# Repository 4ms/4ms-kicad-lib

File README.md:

4ms-kicad-lib
-------------

Intro:
-----

4ms-kicad-lib is a collection of symbol and footprint libraries for KiCad 10.
These libraries were created by and for people working at [4ms
Company](https://4mscompany.com). We share them publicly in hopes they help
others design great circuits. Have fun.

There are also some legacy symbol libraries for KiCad 5.1.x in
`symbols-legacy`, but they will not be updated or maintained, and they aren't
included in the KiCad Plugin and Content Manager archive.

We tried to follow the KiCad Library Conventions, although we made breaks from
that where it made sense. We also tried to keep the look and feel of the
official KiCad symbols, to make using this library and the official KiCad
libraries seamless.

What's in here:
--------------

__Libraries (KiCad PCM archive):__

`symbols`: The symbol library (schematic symbols). As of May 2020, we have
switched to using a unique symbol for each physical component that might appear
on a BOM line.

`footprints`: The footprint library (pcb). Library names tend to follow the
standard of the official KiCad .pretty libraries, but with a "4ms_" prefix. One
interesting library is the `4ms_Faceplate.pretty`: these are intended to be
used with our faceplate generation scripts. Each component is a hole or slot
that's the correct size for a particular faceplate-mounted component. 

`3dmodels`: 3D models for the footprints, organized similar to how the official
KiCad 3dmodels are organized.

__Other stuff (not in KiCad PCM archive):__

`design-blocks`: These are design blocks that we re-use. We're still new to
this workflow, so it's not part of the PCM release until we figure out how to
best package these.

`symbols-legacy/kicad5-2021`: The legacy symbol library for KiCad 5.1.x. This
is a snapshot of the libraries at Nov 19, 2021. It will not be updated or
maintained.

`symbols-legacy/kicad5-2019`: An even older library using non-atomic symbols
(generic resistor, capacitor, etc). This was deprecated in May 2020. It is no
longer maintained or updated.

`footprints-legacy`: The legacy footprint library, not really of much use since
PCBs embed the footprints they used.

`packages3d`: Legacy random 3d models, please verify dimensions before relying
on the accuracy of these models.

`lib-table-files`: The library table files. People working on 4ms projects
should copy these into a project directory (see Option B, Step 3 below).

`schematic-blocks`: KiCad schematic sheets of basic circuits we use over and
over. These building blocks are intended to be used as hierarchical sheets, or
just copy/pasted into your design. They are in KiCad 5 format at the moment but
can be used by KiCad 6 as well.

How to Install Symbol and Footprint Libraries:
----------

There are two ways to install these libraries:

  * **Option A: KiCad's Plugin and Content Manager (PCM).** Easiest. Recommended
    unless you work at 4ms, or are very comfortable with KiCad library management.
  * **Option B: Clone this git repo.** Gets you the latest changes as soon as
    they're pushed, but you have to manually manage this library in KiCad. This
    is what people working at 4ms use.

### Option A: Install with the Plugin and Content Manager

__Step 1) Install the package__

  * In the KiCad project window, open the `Plugin and Content Manager`.
  * Select the `Libraries` tab and find `4ms Kicad Libraries`.
  * Click `Install`, then click `Apply Pending Changes`.
  * Restart KiCad.

KiCad will add all the symbol and footprint libraries to your global
library tables, and the 3D models are installed and linked automatically.

__Step 2) Find the libraries__

PCM adds each library with a `PCM_` prefix on its nickname, so
`4ms_Resistor` shows up as `PCM_4ms_Resistor` in the symbol chooser and
footprint browser. The symbols in the PCM package already link to the
`PCM_4ms_...` footprint libraries, so footprints are filled in for you when you
place a symbol.

__Notes__

  * The footprint links in the symbols assume KiCad's default PCM settings:
    "Automatically add installed libraries to global library table" turned on,
    and "Library nickname prefix" set to `PCM_`. Both are in KiCad's
    Preferences, under `Plugin and Content Manager`. If you've changed either
    of these, you'll need to add the libraries to your tables yourself, using
    the `PCM_` prefix on each nickname.
  * PCM installs files into your `${KICAD10_3RD_PARTY}` folder (on macOS:
    `~/Documents/KiCad/10.0/3rdparty`), in subfolders named
    `com_github_4ms_4ms-kicad-lib`.
  * You can also download the `.zip` from this repo's
    [Releases page](https://github.com/4ms/4ms-kicad-lib/releases) and install
    it with `Install from File...` in the Plugin and Content Manager.
  * Updates show up in the Plugin and Content Manager when we publish a new
    release.

### Option B: Clone the git repo

__Step 1) Download the libraries__

Clone this repo (or download it as a zip) and save it wherever you keep your
KiCad libraries.

__Step 2) Set the `KICAD_4MS_LIBS` path variable__

The footprints find their 3D models through this variable, and the library
table files use it too, so set it even if you add the libraries by hand. You
only need to do this once, it's a global setting.

  * In the KiCad project window, select `Configure Paths...` in the
    `Preferences` menu.
  * Add a new entry named `KICAD_4MS_LIBS`, and set its path to the
    4ms-kicad-lib folder, for example
    `/Users/YOURUSERNAME/MyKiCadProjects/4ms-kicad-lib`

__Step 3) Add the libraries to your library tables__

To add **all** the 4ms libraries to a project (what anyone working at 4ms will
want), copy the two files in `lib-table-files/` (`fp-lib-table` and
`sym-lib-table`) into your project folder. Or you can add those library table files
to an existing project:

Or, to add only some libraries, or to add them globally:

  * Select `Manage Symbol Libraries` (in the schematic editor) or `Manage
    Footprint Libraries` (in the PCB editor) in the Preferences menu.
  * Select the Global tab to use these libraries in all your projects, or
    the Project tab to use them only in the current project.
  * Click the folder icon below the list, and browse to the libraries you want
    to add. On macOS you can Cmd-click to select several at once.
  * Repeat for both the symbol libraries and the footprint libraries.
  * Keep the nicknames as they are (e.g. `4ms_Resistor`), because the symbols
    link to footprints by those names.

### A note on mixing the two

The PCM package and the git repo use different library nicknames
(`PCM_4ms_Resistor` vs. `4ms_Resistor`), and each version's symbols link to
its own footprints. You can have both installed, but stick to one per project,
or a symbol from one may point to a footprint library that the project doesn't
use.

More resources
----------

The symbol library works well with our BOM scripts (exporting files compatible
with JLCPCB, for example). We also have a series of scripts that generate a
Eurorack faceplate from a PCB, and more. These can be found in our script repo:
https://github.com/4ms/4ms-kicad-script

LICENSE
-------

These are in the public domain under the Unlicense.

TODO
----

  * Add better descriptions for each library

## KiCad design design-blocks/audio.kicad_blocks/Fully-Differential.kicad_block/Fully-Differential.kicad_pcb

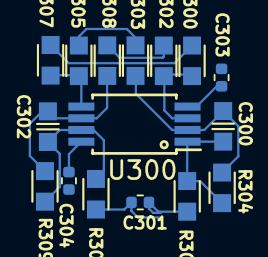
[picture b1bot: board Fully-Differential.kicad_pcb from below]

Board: 2 copper layers, 16 parts (16 on the bottom side), 14 nets.

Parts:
C300, C302: 100pF_0603_50V; C_0603
C301: 10nF_0402_16V; C_0402
C303, C304: 100nF_0402_16V; C_0402
R300, R303, R305, R308: 100k_0603_0.1%; R_0603
R301, R306: 47Ω_0603; R_0603
R302, R304, R307, R309: 14k_0603_0.1%; R_0603
U300: TL072H; TSSOP-8_4.4x3mm_Pitch0.65mm

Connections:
+12V_B: C304.1, U300.8 (V+)
-12VA_B: C303.1, U300.4 (V-)
/Audio/In1_A+: R300.1, R308.1
/Audio/In1_A-: R303.1, R305.1
/Audio/VCOMAD: R302.2, R307.2
/Audio/VIN4+: C301.1, R301.2
/Audio/VIN4-: C301.2, R306.2
GNDA: C303.2, C304.2
unnamed: C300.2, R301.1, R304.2, U300.1
unnamed: C302.2, R306.1, R309.2, U300.7
unnamed: R300.2, R302.1, U300.3 (+)
unnamed: C300.1, R303.2, R304.1, U300.2 (-)
unnamed: R305.2, R307.1, U300.5 (+)
unnamed: C302.1, R308.2, R309.1, U300.6 (-)

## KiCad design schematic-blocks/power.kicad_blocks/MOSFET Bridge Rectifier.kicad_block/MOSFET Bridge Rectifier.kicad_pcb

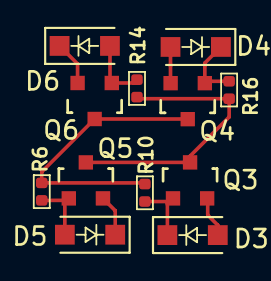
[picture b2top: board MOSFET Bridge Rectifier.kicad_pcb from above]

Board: 2 copper layers, 12 parts (0 on the bottom side), 8 nets.

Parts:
D3, D4, D5, D6: BZT52C12; D_SOD-123F
Q3, Q4: Si2318; SOT23-3_PO132
Q5, Q6: SI2319; SOT23-3_PO132
R6, R10, R14, R16: 10k_0402; R_0402

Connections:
/PWR_SLEEVE: Q4.3 (D), Q6.3 (D), R6.1, R10.1
/PWR_TIP: Q3.3 (D), Q5.3 (D), R14.1, R16.1
GND: D3.2 (A), D4.2 (A), Q3.2 (S), Q4.2 (S)
unnamed: D3.1 (K), Q3.1 (G), R10.2
unnamed: D4.1 (K), Q4.1 (G), R16.2
unnamed: D5.2 (A), Q5.1 (G), R6.2
unnamed: D5.1 (K), D6.1 (K), Q5.2 (S), Q6.2 (S)
unnamed: D6.2 (A), Q6.1 (G), R14.2

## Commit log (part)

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2024-02-27 Set origin to center of component, made vias closer to datasheet hole sizes, and added courtyard
2024-02-27 FP: Added Rocker switch footprint for pod
2024-02-27 SYM: Added rocker switch sym for power pods
2024-03-13 fp: updates to hole size on X_Rock_But_3KD1R202A02RS
2024-03-18 FP: Added Rocker switch with wider holes to lib - SYM: Updated rocker sym with new FP name
2024-03-18 FP: Rocker button - Removed value and extra field from silkscreen.
2024-03-18 SYM: Created nylong standoff symbol with flat base for
2024-04-03 SYM/FP: Added 4KD1R202A02RS rocker switch
2024-04-10 SYM: Added STM32F746IE
2024-09-20 SYM: Added JLC ID to PDS560
2024-09-20 SYM: Removed visibility of JLC ID for PDS560
2024-09-20 SYM: Added JLCPCB ID for RB500SM
2024-09-20 SYM: Added JLCPCB ID for 6.8uH_2.2A_50xx
2024-09-20 SYM: Added JLCPCB ID for 8.2uH_3.2A_6540
2024-09-20 SYM: Added JLCPCB ID for 12uH_5.2A_1260
2024-09-20 SYM: Added JLCPCB ID for AP63356
2024-09-20 SYM: Added JLCPCB ID for TPS54332
2024-09-20 SYM: Removed visibility for JLC ID LMR33630ADDAR
2024-09-26 sym: added 330nf 0603 cap
2024-09-26 sym: added TMUX6208 & TMUX6209
2024-09-30 SYM: Added SSI2164 to lib
2024-10-05 Added BAV99 dual fast switching diode
2024-10-07 created footprints and symbols for all VCAM hardware. Created part for 2x4 SMT header. Created 330nf cap part for VCAM regulator
2024-10-23 SYM: Added JLC ID
2024-10-29 Changed BAV99 to MMBD4148W-7 - part numbers were for 4148 but name was never updated
2024-10-29 SYM: Added display field to small jacks
2024-11-01 FP: Added faceplate SD card slot
2024-11-01 Updated Hardware symbol library to Kicad 8
2024-12-06 SYM: Added STM32MP135F-DK
2024-12-06 SYM: Added RGB Encoder from SWN to new library
2024-12-06 Updated field visibilties for BAT54 diode
2024-12-18 Added RoHS, CE, and WEEE logos to library
2024-12-18 SYM: Added mfr and part number to MC33078
2024-12-20 SYM: Added Filshu to switch mfr field
2024-12-23 added omron relay
2024-12-23 Fixing merge conflicts
2024-12-23 added quarterinch stereo jack
2024-12-24 added SPST footswitch
2025-01-02 Resolved sym lib issue
2025-01-02 added right angle DC jack
2025-01-02 added 7660 to library
2025-01-10 Added SerialNumberPlacement Footprint
2025-01-14 fixed pin 1 on 7660S
2025-01-17 added CY8CMBR3116
2025-01-21 added capsense pad
2025-01-21 Added ASPI-4030S-8R2M-T inductor
2025-01-21 working on capsense part
2025-01-21 capsense pad work in progress
2025-01-22 Added pin1 or pad1 to capsense footprint. Made schematic sym a little more easy to visualize on schematic side
2025-01-22 Added inductor syms and matching footprints
2025-01-22 Removed JLC field from visibility
2025-01-24 fp: Add DaviesKnob
2025-01-24 fp: add jumper SMD 1x3 shorted 1-2
2025-01-24 fp: Update jumper1x3 (unshorted)
2025-01-24 Added POD specific euro header sym
2025-01-27 Replaced 330nF 25v - old part had conductive epoxy termination
2025-02-14 Added 3D models for PKS-01L-X button and PER231 Potentiometer. Added sym and FP for PER231 potentiometer
2025-02-14 Adding 3D footprints for the handheld unit
2025-02-14 Set PER231 origin to center of component. Adjusted 3D mode Z axis for Screen part
2025-02-26 Added JST 2pin connector for LiPo batteries
2025-02-28 Added LiPo battery management ICs to sym and added S-PDSO to footprint library
2025-03-21 Adding library parts for USBC LiPo charger
2025-03-27 Added parts for handheld
2025-04-11 wip TAC5211
2025-04-15 WIP - codec
2025-04-18 Codec WIP
2025-04-29 FP: fix SMD coils set to TH
2025-04-29 FP: update slotted barrel jack (was set to SMD, should be TH)
2025-05-05 Added 3.55mm horizontal stereo switching jack sym-fp-3d, fixed an battery related IC a regulator
2025-05-20 SYM: Added 5.6uH 3.15A inductor
2025-06-04 sym: connectors: add 2x40 high-speed 0.4mm socket and pins, ...
    - Add Molex 2171790001 USB C jack
    - Add right-angle 1x2 2.54mm header
2025-06-04 fp/3d: add models for connectors from last commit
2025-06-04 fp: add generic 3mm mounting hole
2025-06-04 sym: IC: add JLC id for AP2300
2025-06-04 sym: Switch: add JLC ids for tact switches
2025-06-06 Updated parts to resolve DRC errors
2025-06-10 Added W2Q128JV flash chip
2025-06-10 Added 12mhz 15pf crystal
2025-06-10 added NCP1117 3v3 regulator
2025-06-10 filled in missing fields for NCP1117
2025-06-11 Revert "Added sym and FP for PER231 potentiometer" (corrupted)
    This partially reverts commit 416beb4f503b0d3cb1dfbcb3268bd02eb172823e.
    The commit corrupted the Potentiometer symbol library file
2025-06-11 Merged footprint updates created in mm-handheld branch
2025-06-11 Added 75ohm 500mW resistor
2025-06-12 Added RP2350
2025-06-12 added eight inch right angle smt jack
2025-06-12 changed view for right angle eigth inch SMT jack
2025-06-12 Added PCM1754DBQR
2025-06-12 Added NCS20072DTB
2025-06-12 Added 9mm RGB SPST button
2025-06-18 Remove empty file
2025-06-18 sym: Make NCS20072 power pin locations identical to other opamps
2025-06-18 sym: Make PCM1754DBQ derive from PCM1753
2025-06-19 fp: SOIC-8 remove silk from soldermask
2025-06-24 sym: add ER-TFT3.99-1 (400x960 rgb parallel display)
2025-06-24 sym: add crystal - ABM8_272_T3
2025-06-24 sym: add regulator - TLV61070ADBVR
2025-06-24 fp: add tft3.99 400x960 display
    the footprint has an extra long fpc connector for prototyping
2025-06-25 sym: add 4.7uf 0603 cap
2025-06-25 fp: tft3.99 update anchor pos
2025-06-26 sym: Update LED library to kicad v9
2025-06-26 sym: add JLC number to 4.7uH 1.7A inductor
2025-06-26 sym: connector P2.54mm: add 2x3 rt angle, 2x6 vert, 2x6 rt angle, 2x4 socket
2025-06-26 fp: add 2x3 and 2x6 2.54mm rt angle connectors
2025-06-26 sym: add regulator - TLV62569DBV
2025-07-01 fp: add pb20b variant without pins 3,4
2025-07-03 sym: Fix use of local fp in 2x40 connectors
2025-07-03 fp + 3d: add 2x40 0.4mm x 3mm connectors
2025-07-03 fp: USB-C molex jack add 3d model link
2025-07-11 fp: add some large BGAs
2025-07-11 fp: Fix 1/8" jack silk overlap warning
2025-07-11 sym: 4.7uH 1.7A inductor: add second P/N
2025-07-11 sym: PKS-01-BK button added
    Was used in previous projects, but as a generic PB20 button
2025-07-11 sym: IC: add STM32MP257DAL
2025-07-17 sym: fix AP62300Z6 part number (missing -7 suffix)
2025-07-17 sym: 4.7uF_0603_10V fix: do not derive
2025-07-17 sym: cleanup appearance of stereo jack
2025-07-17 fp: clean up silkscreen (ER-TFT3.99)
2025-07-17 fp: change pin names (Jack_3.5mm_CUI)
2025-07-17 fp: increase thermal via size (RP2350-60)
2025-07-17 fp: shrink pads (Button_SPST_RGB_9mm)
2025-07-18 sym: Fix DDR3L RAM part number suffix
2025-07-29 sym: Fix typos in field names
2025-07-29 sym: Add JLCPCB numbers for some inductors
2025-08-12 sym+fp: Add mp153 dev board v0.2
2025-08-12 3d: add mp153 devboard
2025-08-22 WIP - MM Handheld parts - mic
2025-09-05 Connected MP23DB01HP to footprint - updated footprint to have copper ring attached to pad 3
2025-09-06 Moved sym pins for the layout to make more sense
2025-09-07 SYM/FP: Added LIS2HH12TR accelerometer and LGA-12 footprint to 4ms library
2025-09-14 Moved fp for screen connector into 4ms library and updated schematic part field to use 4ms version of connector
2025-09-16 sym: Added BQ24073 and BQ27220 to IC lib - FP: Added DSBGA-9 BGA footprint to FP lib
2025-09-16 SYM: Updated BQ24073
2025-10-06 Added wip-screenstandoff - needs to be finished
2025-10-06 Removed wip-screenstandoff (moved to project library)
2025-10-08 sym/fp: add AS11CH slide switch
2025-10-08 sym/fp: add LM4666 and WSON-14
2025-10-08 sym/fp: add new screws
2025-10-08 fp: connector for ERTFT3.99
2025-10-08 SCH/FP: Added EN12-HSSAF18 encoder sym, fp and 3D file
2025-10-08 SYM/FP: Added B3F-4055 button to library w/ 3D Model
2025-10-08 SYM/FP: Updated EN12-HS22AF18 with correct pin numbering
2025-10-13 Devboard A/B: set XY pos to center of headers
2025-10-13 IC sym: fix some pin types and 0-height fonts
2025-10-13 sym+fp: BQ27441: Fix different names for EP. Use VSON-12 for fp name
    VSON-12 is what it's called in the datasheet
2025-10-13 sym: update diodes lib to kicad 9. Change BAT54S alt JLC number field name
2025-10-14 fp: VSON-12 EP thermal hole size => 0.3mm
2025-10-14 fp: RHLGA-5: add mask opening for pad 3 (ring/gnd)
2025-10-17 SYM: Added LP5009PWR LED driver to library
2025-11-03 fp: add Adafruit_pcm5100a
2025-11-07 FP: Added 14hp rail connection
2025-12-01 sym: LP5009: fix pin types
2025-12-11 SYM: Added yellow LED
2025-12-12 SYM-FP: Added Small tactile switch
2025-12-13 Fixed 3D placement for tact switch
2025-12-13 FP: Added faceplate hole for 5mm tact twitch
2025-12-14 Created mp153 footprints with silk instead of guide holes
2025-12-14 FP: Added correct pin numbers for Tact swithc
2025-12-15 sym: Add RCA jacks
2025-12-15 sym+fp: add Right-angle RGB APFA2507LQBDSEEZGKC
2025-12-15 fp: add motorized slider footprint
2025-12-15 sym: Add motorized slider
2025-12-18 SYM: PCM3060PW changed VCOM pin to passive
2025-12-18 FP: LED 0603 - removed visibility of value field
2025-12-18 FP: EigthInch_Stereo_PJ366ST - removed visibility of value field
2025-12-19 fp+3d: add Switchcraft PJRAS2X1S stereo RCA jack
2025-12-19 sym: JLCPCB number for DRV8210DRLR
2025-12-19 sym: link footprint for stereo RCA jack
2025-12-20 sym: add TLV320AIC3204
2025-12-20 sym/fp: fix pin number mismatch for motorized pot
2025-12-20 sym: cleanup jack pin name position
2025-12-27 SYM: Added Display field to Open solder jumper - makes it easier to label jumper on silk without it being in the value field
2025-12-27 FP: Added 2x40 th pin connector
2025-12-28 SYM: Added TH 2x40 pin connector sym
2025-12-29 sym: add JLC number to PCM3060 codec
2026-01-02 sym: fix DRV8210 pin type
2026-01-02 sym: mp153-devboard add graphics for pull-ups and switch
2026-01-02 fp: add JLC ID for TLV74018
2026-01-13 sym: add JLC IDs
2026-02-18 sym: add 128MB DDR3 (MT41K64M16TW)
2026-02-18 sym: Add STM32MP135DAF7
2026-02-21 fp: add 2x5 1.27mm socket
2026-02-21 fp: add QFN-56
2026-02-21 sym: add 2x5 1.27mm socket
2026-02-21 sym: add various power symbols
2026-02-21 sym: add STM32MP257 and STPMIC2
2026-02-23 sym: add 0.68uH and 2.2uH inductors
2026-02-23 sym: add DDR4 16Gbit
2026-02-23 sym: add 40MHz xtal
2026-02-23 sym: add 10uF/0402, 2.2uF/0201, 4.7uF/0201
2026-03-05 FP: Updated courtyard on euroheader to not flag DRC error
2026-03-05 FP: Added courtyard to testpoint
2026-03-05 FP: Fixed logos to not flag DRC warnings
2026-03-05 FP: Resolved silkscreen overlap DRC warnings for components
2026-03-11 sym: Update AP2120 regulator JLC ID
2026-03-11 sym: fix part number of TL1105 round black button
2026-03-11 sym: add 240Ω 0201
2026-03-11 fp: Add 30-pin b2b connector
2026-03-11 fp: add c0201 footprint
2026-03-12 FP: Fixed orientation of 3D model
2026-03-12 SYM: Added 4.55mm 2x4 SMD Socket
2026-03-12 SYM: Added 4.55mm 2x5 SMD Socket
2026-03-12 sym: add 2x5 1.27mm socket (4.5mm height)
    Samtec FLE-105-01-G-DV-K
2026-03-12 SYM: Updated fields for STM32MP135DAF7 to be output correct information in BOM generation
2026-03-13 sym+fp+3d: mezzanine connecctor 40pin
2026-04-02 sym: cap: add some p/n
2026-04-02 sym:ic: fix mp257 fields
2026-04-02 sym: inductor: fix fp field
2026-04-02 sym: cap: add missing p/n
2026-04-02 sym: res: add p/n
2026-04-06 sym: Add 2x20 mezzanine and ZPYxx zener
2026-04-06 sym: P/N for crystals
2026-05-13 Added Cherry switches for prototyping
2026-06-03 Added sym, fp, and 3d model for MIDI jack
2026-06-04 Created Faceplate_Hole_MIDI_DIN5_SD-50BV.kicad_mod
2026-06-04 Increased height of 4hp 5hp and 6hp rail connections to 8mm instead of 6mm, to match other rail connection parts
2026-06-05 Added 2x6 SMD pinheaders
2026-06-16 sym: add ER-OLED1.09 symbol
2026-06-17 sym: add dac tlvDAC3203
2026-06-17 update symbol lib
2026-06-19 sym, fp: add 1TS009 switch
2026-06-19 sym: add 74hc138
2026-06-19 sym: add aps6404-3sqr IC
2026-06-19 fp: add ER-OLED1.09
2026-06-19 sym: add fp and JLCPCB ID to ER-OLED
2026-06-23 Added sym and fb parts for 1x05 sockets/headers and 1x04 sockets/headers with 3d models
2026-06-26 Add MCP6001 IC
2026-06-29 fp: CUI_SJ-3523 update courtyard
